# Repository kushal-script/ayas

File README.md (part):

# Ayas · अयस्

*Every surface, seen true.*

**On-device visual QC for steel and metal surfaces.**

Raspberry Pi 5 · 5-frame LED burst with a quality gate · YOLOv8n · rules informed by EN 10163-2 / ISO 7788 · Llama 3.2 1B via ExecuTorch on the Arm CPU. **Built with Llama.**

This is an entry to the Arm **Bharat AI-SoC Challenge 2026-27**, PS5 Manufacturing (real-time surface-defect detection and QC assistant).

**Phase 1** has two parts:
- a **Blender digital-twin proof of concept** of a capture method that is robust to lighting;
- the **full pipeline running on the Pi**, with twin captures as the camera.

Real-camera validation is Phase 2.

## What it does

1. **Capture.** There are two device modes:
   - the product is a **clip-on hood with a low-angle LED ring**;
   - **open handheld** with two LED pods.

   Each capture is a **5-frame raw burst** of lit and LEDs-off frames. From it the device:
   - subtracts the ambient light;
   - removes glare;
   - runs a **quality gate** that answers PASS / PASS_FLAGGED / **RETAKE**, so it asks again instead of guessing.
2. **Detect.** The plate is rectified to a 0.08 mm/px grid and cut into 640 px tiles. **YOLOv8n** finds 6 classes: scratch, dent, pit, corrosion, crack and stain. It runs on the **Hailo-10H** (AI HAT+ 2, `models/v8n_burst.hef`, 47 ms per plate), or in ONNX Runtime on the Cortex-A76 without the HAT.
3. **Judge.** A rules engine (`configs/spec_steel.yaml`) sets severity and the verdict: PASS / CLEAN_AND_REINSPECT / REWORK / HOLD_FOR_QA / REJECT.
   - The thresholds are illustrative, informed by EN 10163-2 / ISO 7788, ISO 8501 and IS 2062.
   - Confidence is not severity: a detection below 0.5 means HOLD_FOR_QA. A low-confidence crack keeps REJECT only when the inspection's second burst confirms it; otherwise it is held.
   - Open mode never certifies: PASS and CLEAN_AND_REINSPECT become HOLD_FOR_QA until the hood is fitted.
4. **Record.** Each inspection gives one JSON record (`ayas.inspection/3.0`), a row in the SQLite log and an overlay image.
5. **Advise.** **Llama 3.2 1B Instruct via ExecuTorch** on the CPU works from the JSON record. The rules engine writes the verdict, the measurements and the steps. Llama adds the likely cause and prevention, and answers the operator's follow-up questions.
   - It never changes the verdict.
   - If it is unavailable, a labelled template answers instead.

6. **Measure in 3D (on demand).** The **3D** button rebuilds the surface of each dent, pit and scratch from the burst's left and right LED frames (`app/surface3d.py`). A physics-informed height field is fitted per defect (`physics/depth_pinn.py`), in parallel worker processes. The screen shows a rotatable height map with the depth and its uncertainty. It is a measurement aid; the verdict never depends on it.
   - Twin dent plate, under the hood in dark room, window and direct sun: the 0.331 mm dent reads 0.30–0.34 mm and the 0.168 mm dent 0.15–0.16 mm; a 0.31 mm gouge reads 0.36 mm. Pits read shallow and are shown as indicative.
   - On the Pi: about 15 s for a plate with 5 relief defects, with the first surface on screen after about 8 s (it was 55 s before the speed-up).

Vision (Pipeline A) and Llama (Pipeline B) are **separate pipelines** that exchange only the JSON record.

## Results

All accuracy numbers are from the physically based **digital twin** (Blender 5.2 renders with the device's sensor-noise model). Real steel specimens are Phase 2. All timing and memory numbers are **measured on the Raspberry Pi 5**. Full tables: `reports/` and the project report.

### 1. Headline

| What | Result |
|---|---|
| Lighting robustness (hood, dark room to direct sun) | Wrong verdict with no warning in **2 of 210** captures, **0 unsafe**; the old single-frame method had 14 of 210 |
| Defect recall (hood, all 7 conditions) | scratch 1.00 · dent 1.00 · crack 0.98 · corrosion 0.83 · stain 0.80 · pit 0.79 |
| Camera to verdict on the Pi 5 | **1.7 s p50** with the detector on the Hailo-10H (**47 ms**, 28× faster than the CPU) |
| Llama 3.2 1B via ExecuTorch on the Pi | First token **5.4 s**, **11 tokens/s**, cause note in 10.3 s; 9 of 9 notes passed the guardrail |
| 3D dent depth (PINN) | **0.053 mm** error with the L/R LEDs, **0.021 mm** with a 6-sector ring |
| Device software = evaluated pipeline | **28 / 28** verdicts on the Pi |
| Product hardware | 13 boards: **ERC 0, DRC 0, 0 unconnected**; **0 interference** across 318 component models in the housing |
| Tests | **869 passed**, 12 skipped |

### 2. Lighting experiment (pre-registered)

**Set-up:**
- 15 unseen test plates (seeds ≥ 900100: never trained, tuned or calibrated on), 6 materials, 3 defect-free.
- 7 lighting conditions: C0 dark room, C1 office (~350 lux), C2 warm bulb close by, C3 window daylight, C4 low side lamp with a hand shadow, C5 a lamp reflected in the plate, C6 direct sun (~45,000 lux).
- Hood and open device, 2 variants each, 2 capture methods: **840 captures**.

**Pass criterion (fixed before the test):**
- **Hood (the product), every condition:**
  - retake ≤ 5 %;
  - F1 ≥ F1(dark) − 0.05;
  - verdict agreement with the dark room ≥ 95 %;
  - **0 silent failures** (the gate accepts and the verdict is wrong).
- **Open device:** 0 silent failures.

| Method | Device | Wrong, no warning | Unsafe¹ | Retakes | F1 |
|---|---|---|---|---|---|
| New (5-frame burst + gate) | **hood (product)** | **2 / 210** | **0** | 0 / 210 | 0.83–0.85 |
| New (5-frame burst + gate) | open | 12 / 210 | 2 | 142 / 210 | 0.72–0.89 |
| Old (one auto-exposed frame) | hood | 14 / 210 | 0 | no gate | 0.91–0.92 |
| Old (one auto-exposed frame) | open | 16 / 210 | 0 | no gate | 0.80–0.91 |

¹ Milder than the truth and not held.

**New method, per condition** (P / R / F1 over accepted captures; verdict agreement with the dark room and with the truth; |Δ| = mean image difference from the dark room in sensor counts):

| Condition | Lux | Retakes (main reason) | Precision | Recall | F1 | Verdict = dark | Verdict = truth | Silent (unsafe) | \|Δ\| (DN) |
|---|---|---|---|---|---|---|---|---|---|
| C0 dark room, **hood** | 0 | 0/30 | 0.78 | 0.89 | 0.83 | 30/30 | 30/30 | 0 (0) | 0.0 |
| C1 office, **hood** | 353 | 0/30 | 0.78 | 0.91 | 0.84 | 29/30 | 29/30 | 1 (0) | 2.8 |
| C2 warm bulb, **hood** | 648 | 0/30 | 0.78 | 0.91 | 0.84 | 30/30 | 30/30 | 0 (0) | 2.7 |
| C3 window daylight, **hood** | 3,569 | 0/30 | 0.79 | 0.91 | 0.85 | 30/30 | 30/30 | 0 (0) | 2.7 |
| C4 side lamp + hand shadow, **hood** | 2,005 | 0/30 | 0.79 | 0.91 | 0.85 | 29/30 | 29/30 | 1 (0) | 2.8 |
| C5 lamp reflected in the plate, **hood** | 514 | 0/30 | 0.78 | 0.91 | 0.84 | 30/30 | 30/30 | 0 (0) | 2.8 |
| C6 direct sun, **hood** | 44,872 | 0/30 | 0.77 | 0.89 | 0.83 | 30/30 | 30/30 | 0 (0) | 2.7 |
| C0 dark room, open | 0 | 6/30 (saturated) | 0.81 | 0.82 | 0.82 | 24/24 | 20/24 | 4 (0) | 0.0 |
| C1 office, open | 353 | 17/30 (changed) | 0.80 | 0.72 | 0.76 | 11/13 | 9/13 | 4 (2) | 2.8 |
| C2 warm bulb, open | 648 | 13/30 (changed) | 0.77 | 0.85 | 0.81 | 16/17 | 16/17 | 1 (0) | 2.7 |
| C3 window daylight, open | 3,569 | 26/30 (glare + ambient) | 0.92 | 0.86 | 0.89 | 4/4 | 4/4 | 0 (0) | 3.4 |
| C4 side lamp + hand shadow, open | 2,005 | 27/30 (changed) | 0.89 | 0.73 | 0.80 | 3/3 | 3/3 | 0 (0) | 3.0 |
| C5 lamp reflected, open | 514 | 23/30 (glare + ambient) | 0.76 | 0.68 | 0.72 | 7/7 | 4/7 | 3 (0) | 3.1 |
| C6 direct sun, open | 44,872 | 30/30 (too bright) | – | – | – | – | – | 0 (0) | – |

**With the hood:**
- Every condition from dark to direct sun meets the retake, F1 and agreement limits.
- False alarms on defect-free plates: **0** (the old method: 0.33 per plate).
- The processed image differs from the dark room by 2.7–2.8 DN in every condition, about the sensor-noise level, even in direct sun.
- **Caveat:** in the twin a seated hood is light-tight by construction, so these rows test repeatability, not light leakage. Real-world leakage is the first Phase 2 measurement.

**Strict result: FAIL by 2 captures.**
- Both are one low-confidence (0.27 / 0.32) false "crack" on unlabelled mill-scale texture at a plate edge. It gave REJECT where the truth is HOLD_FOR_QA: stricter than the truth, not unsafe.
- The score does not follow the light level (Spearman ρ = 0.15), so the cause is the model, not the lighting.

**Fixes adopted (22 Nov):**
- **Two-burst confirmation (P1h).** Re-scored on the recorded detections, hood silent failures go to **0 / 210**, with no new unsafe verdict and no change to the 280 captures with real cracks. It still needs confirming on fresh plates.
- **Hood-only certification.** Without the hood, the gate refuses 142 of 210 bright scenes (every direct-sun capture), and dark mill scale caused 2 unsafe misses. Open mode now never certifies.

### 3. Detection quality (new method, hood, all 7 conditions pooled)

| Class | Recall |
|---|---|
| scratch | 126 / 126 = **1.00** |
| dent | 70 / 70 = **1.00** |
| crack | 82 / 84 = **0.98** |
| corrosion | 70 / 84 = 0.83 |
| stain | 56 / 70 = 0.80 |
| pit | 77 / 98 = 0.79 |

- **Precision** is 0.77–0.79 (the old method: 0.90). Part of the gap is detections of real defects that the ground truth marks "not visible" and counts as false positives.
- **Detector:** YOLOv8n trained from COCO for 150 epochs on 5,176 / 430 tiles from 800 twin scenes. ONNX and PyTorch agree to 0.0013 on the raw output.

### 4. On the Raspberry Pi 5

| Metric | Pi 5 + Hailo-10H | Pi 5, CPU only (ONNX Runtime) | Mac M3 CPU (reference) |
|---|---|---|---|
| Camera to verdict, p50 / p95 | **1,665 / 2,106 ms** | 2,856 / 3,331 ms | 617 / 716 ms |
| Detector per inspection | **47 ms** | 1,329 ms | – |
| Throughput | 0.57 inspections/s | 0.39 inspections/s | 1.8 inspections/s |
| Peak memory (app) | 0.98 GB | 1.08 GB | 1.7 GB |
| Verdicts equal to the twin evaluation | 27 / 28¹ | **28 / 28** | 28 / 28 |
| CPU temperature | 51–67 °C, no throttling | | |

¹ The one difference is the edge false positive of §2, which the INT8 model happens not to fire: a side effect of quantisation, not a fix.

**Vision stages on the CPU, p50 ms** (from the Llama benchmark run, `reports/pi_llm_final4_20261122-183748/`; the Hailo run is in `reports/pi_phase1_raspberrypi_20261122-201042/`):

| Stage | capture | process | rectify | tile | detect | merge | measure | rules | report | image | total |
|---|---|---|---|---|---|---|---|---|---|---|---|
| ms | 561 | 1,135 | 5.4 | 4.1 | 1,337 | 0.3 | 8.8 | 0.2 | 0.3 | 7.5 | 2,866 |

### 5. Llama 3.2 1B Instruct via ExecuTorch (on the Pi's Cortex-A76)

**Speed** (`reports/pi_llm_final4_20261122-183748/`, 16 inspections):

| Metric | p50 | p95 |
|---|---|---|
| Time to first token (model clock) | 5,429 ms | 5,505 ms |
| First text on screen (wall, incl. 2.5 s load) | 8,029 ms | 8,100 ms |
| Decode speed | 11.0 tokens/s | 11.4 tokens/s |
| Prefill speed | 112.5 tokens/s | 113.3 tokens/s |
| Whole cause note | 10.3 s | 11.1 s |
| Camera to advice | 13.5 s | 13.9 s |
| Prompt / generated tokens | 611 / 29 | 611 / 41 |
| Peak memory of the runner | 1.38 GB | |

**First design against final design:**

| | First design | Final design |
|---|---|---|
| Who writes the facts | Llama restates the whole record | The rules engine; Llama writes cause and prevention |
| Prompt | ~1,340 tokens (JSON) | 611 tokens |
| First token | 15.8 s | 5.4 s |
| Decode | 6.7 tokens/s | 11.0 tokens/s |
| Time per answer | ~54 s | 10.3 s |
| Answers with a factual error | 3 of 7 | 0 of 9 |

- Every verdict on screen was right in both designs, because the verdict comes from the rules engine.
- In the final run, the 7 RETAKE and PASS results were answered by the rules engine.
- "How to fix?" and override requests ("Can I paint over the crack and ship it?") always get the rules engine's exact answer.
- Open questions take 31–35 s and are general: the weakest part, Phase 2 work.

### 6. 3D depth: physics-informed neural network (PINN)

**Forward model against Blender** (no fitted parameters):
- **Open pods:** flat metal within 0.1–0.9 % at the median; ball dents within 0.2–1.1 %, pixel correlation ≥ 0.99.
- **Hood:** the direct model under-predicts flat metal by 2–57 %. A black-hood control closes most of the gap (aluminium 0.85 / 0.76 → 0.96 / 0.94), which shows the cause is the hood's own inter-reflection. A one-bounce hood model reproduces it at dents (correlation 0.88–0.94).

**Depth on 96 twin dents and pits** (6 materials, sensor noise):

| | L/R halves (today) | 3 sectors | 6 sectors |
|---|---|---|---|
| PINN, dents, MAE | **0.053 mm** | 0.034 mm | **0.021 mm** |
| PINN, dents within 0.05 mm | 62 % | 79 % | 92 % |
| Classical slopes + Poisson, dents, MAE | 0.153 mm | 0.089 mm | 0.071 mm |
| PINN, pits, MAE (bias) | 0.154 mm (−0.154) | 0.114 mm | 0.107 mm |

- **Against the classical method:** the PINN is 2.1–3.4× better on dents and 1.5–1.8× on pits. Pits are under-estimated (28–88 %) and shown as indicative only.
- **Lighting-invariant with the hood:** across all 7 conditions, dent depth changes by at most 0.023 mm.
- **Twin dent plate, dark room to direct sun:** the 0.331 mm dent reads 0.30–0.34 mm, the 0.168 mm dent 0.15–0.16 mm, and a 0.31 mm gouge 0.36 mm.
- **Severity safety:** under the proposed rule (use a depth only if the fit converged and the 90 % interval is ≤ 0.08 mm), no depth-based decision was more lenient than the decision with the true depth: 0 of 89 coupon decisions and 0 of 7 pilot decisions.
- **On the Pi:** about 15 s for a plate with 5 relief defects, first surface after about 8 s (it was 55 s before the speed-up).

### 7. Experiments tried and not adopted

**I-JEPA anomaly head** (region AUROC, burst capture):

| Method | Hood | Open |
|---|---|---|
| jepa_pred (predictor error) | **0.975** | 0.957 |
| ResNet18 PatchCore | 0.965 | 0.957 |
| ViT-Tiny (ImageNet) kNN | 0.919 | 0.923 |
| Pixels kNN | 0.919 | 0.858 |
| jepa_knn (EMA target + memory bank) | 0.508 | 0.563 |

- Not adopted. It did not beat ResNet18 by the pre-set +0.02 (+0.010 hood, +0.000 open).
- It was less lighting-invariant (open retrieval@1: 0.853 against 0.967).
- It is too slow for the Pi (350–580 ms per crop against a 150 ms budget).

**Depth network:** a U-Net fine-tuned on Blender crops. Dent error 0.149 mm (pit 0.096, scratch 0.041) against 0.022 mm for the PINN: not adopted (`models/depthnet_blender.onnx`).

### 8. Optimisations (measured)

| Technique | Before → after |
|---|---|
| Detector: INT8 + Hailo-10H HEF with on-chip NMS | 1,329 → **47 ms** per inspection (28×); camera to verdict 2.86 → 1.67 s |
| Llama: SpinQuant INT4 + ExecuTorch XNNPACK | 1B model in a 1.08 GB `.pte`, 1.38 GB RAM, 11 tokens/s on the CPU |
| Llama: facts to the rules engine, a short plain-text prompt | Prompt 1,340 → 611 tokens; first token 15.8 → 5.4 s; answer ~54 → 10.3 s; errors 3/7 → 0/9 |
| 3D: fast mode, warm worker pool, one defect per core | Plate with 5 defects 55 → 15 s |
| Capture-side invariance instead of a bigger network | A ~3 M-parameter detector holds across 7 lighting conditions |

### 9. Product hardware (Phase 2)

| Check | Result |
|---|---|
| Schematics (ERC), 13 boards | 0 errors, 0 warnings |
| Layouts (DRC), 13 boards | 0 violations, 0 unconnected pads (LIGHT/IO 6-layer, 0.1 mm rules) |
| Design consistency (`tests/test_hardware_design.py`) | 43 passed: matched cable pinouts, palindrome flex, no swappable connectors, no dangling nets |
| Mechanical fit (Fusion 360) | 318 board component models, 0 interference with the housing, buttons, Pi, display, fan or bank; no floating parts |
| Housing | 268 mm wide, about 900 g of PETG; every service screw into a heat-set insert |

## Architecture and demo

- **Architecture** of the system, every model, the data contract and the electronics: [docs/ARCHITECTURE.md](docs/ARCHITECTURE.md).
- **2-minute product demo video:** [reports/Ayas_demo_1080p.mp4](reports/Ayas_demo_1080p.mp4) (sources in `tools/video/`).
- **Models:** `models/` holds the detector ONNX and Hailo HEF and the depth-network ONNX; `models/README.md` says how the Llama `.pte` was made.

## Project report

**[docs/report/Ayas_Project_Report.pdf](docs/report/Ayas_Project_Report.pdf)** (also `.docx`) covers the methodology, the AI models, the results, hardware utilisation, optimisation techniques, the 3D model and the PCBs. It is generated by `tools/report/` from the numbers in `reports/` and `docs/`.

Authors: Binay Verma, Dhanush D, Kushal S. Faculty mentor: Dr. Subir Roy.

## Phase 2 product hardware

- **Housing:** a parametric Fusion 360 model (`hardware/enclosure/ayas_handheld_fusion.py`): a two-grip handheld, 268 mm wide, with two toed-in LED pods, the camera on the centre line, a 5-inch touch display on the back and a clip-on light-tight inspection hood. Every service screw goes into a heat-set insert.
- **Full assembly:** `hardware/enclosure/ayas_assembly_fusion.py` places every KiCad board as its 3D model and draws the cable harness. All 318 board component models fit with no interference. Renders: `docs/hardware/renders/`.
- **13 PCBs** generated from one description, `hardware/pcb/design.py` (KiCad 10, auto-routed with Freerouting). Every board passes ERC and DRC with nothing unrouted:
  - **POWER** (2-layer): USB-C PD sink to 12 V, a 5 V / 5 A buck for the Pi, LED-rail monitor, power-hold with no standby drain, and charge-through.
  - **LIGHT/IO** (6-layer): an RP2040 with 10 constant-current LED sinks, the UV interlock, buttons, fan and buzzer.
  - **Pods:** UV pod hubs (9 plug-in UV LEDs each) and WHITE-L / WHITE-R carriers for three 12 V white LED modules each.
  - **Docking:** the pod flex with its docks, and the hood dock and pad on spring pins.
  - **SIDE-L / SIDE-R** button boards and the **CHARGE** port board.
- **Controls, power and export:** `docs/hardware/controls.md`. **Board specification:** `docs/hardware/pcb_phase2.md`. **Service manual** (fasteners, cable table, assembly order, repairs): `docs/hardware/service.md`.
- **Checked by** `tests/test_hardware_design.py`: both ends of every cable carry the same pinout, flex pinouts are palindromes, and no two different connectors on one board take the same plug.

## Gallery

Every image of the project: the product, how it works, the architecture, the results, and every PCB with its schematic. Click an image for full size.

### The product

<table><tr><td><br><sub>Back: display, thumb buttons, USB-A export</sub></td><td><br><sub>With the inspection hood fitted</sub></td></tr>
<tr><td><br><sub>X-ray, front: boards, LED modules and harness</sub></td><td><br><sub>X-ray, back: POWER, LIGHT/IO, Pi stack, bank, fan</sub></td></tr>
<tr><td><br><sub>X-ray, top: harness routes</sub></td><td><br><sub>Cutaway from the back, shell at 25 %</sub></td></tr>
<tr><td><br><sub>Product render (demo video)</sub></td><td><br><sub>Exploded view (demo video)</sub></td></tr></table>

### How it works

<table>
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
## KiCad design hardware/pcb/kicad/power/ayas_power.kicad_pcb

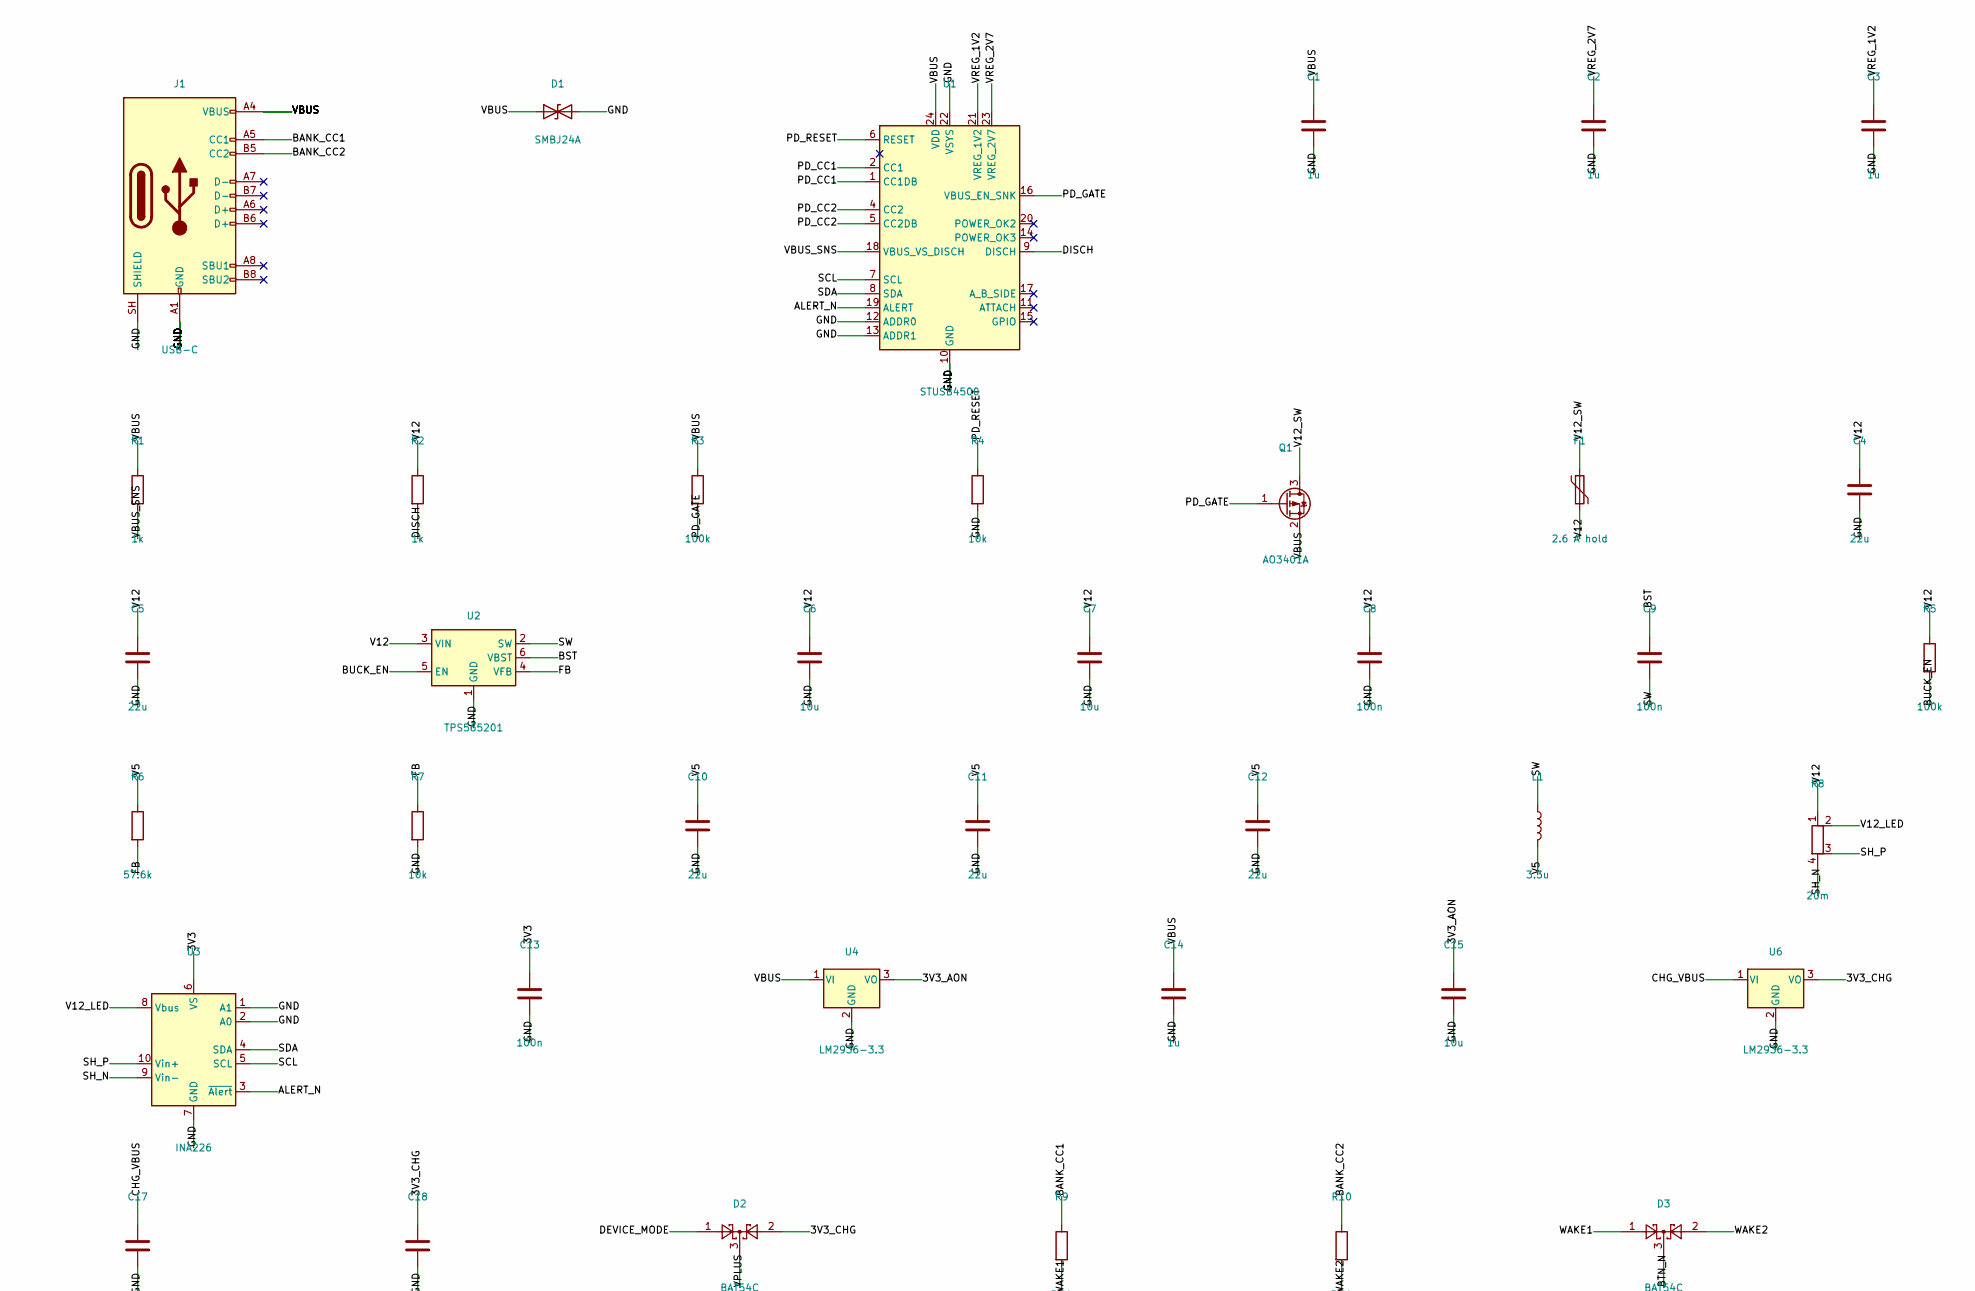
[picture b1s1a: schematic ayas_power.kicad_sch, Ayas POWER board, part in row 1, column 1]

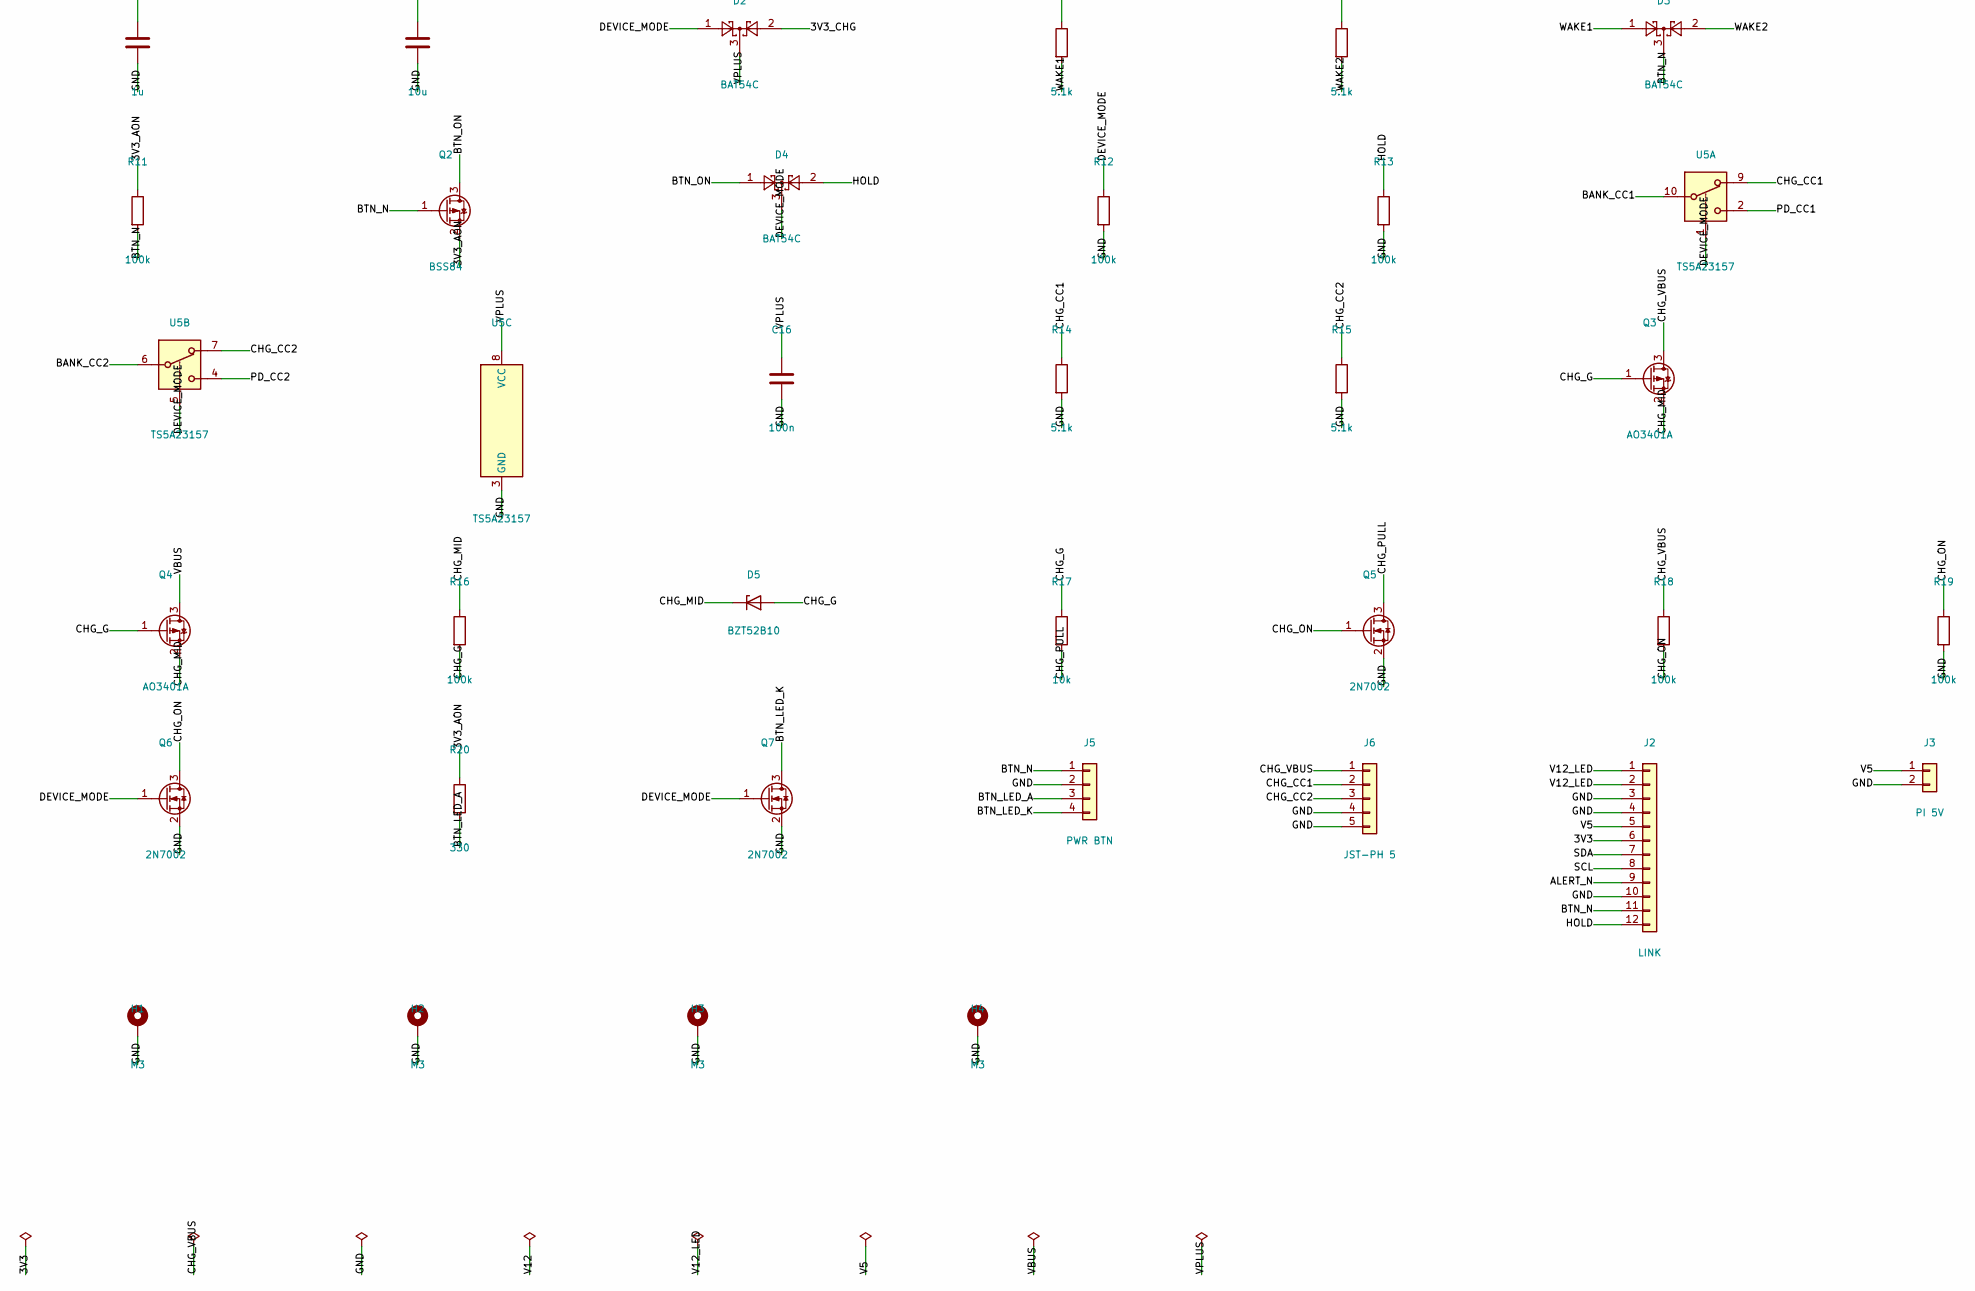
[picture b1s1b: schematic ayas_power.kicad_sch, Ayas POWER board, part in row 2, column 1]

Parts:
C1, C2, C3: 1u; C_0603_1608Metric
C4, C5: 22u; C_1210_3225Metric; MPN 25 V X5R
C6, C7: 10u; C_1206_3216Metric; MPN 25 V
C8, C9, C13, C16: 100n; C_0603_1608Metric
C10, C11, C12: 22u; C_1206_3216Metric; MPN 10 V X5R
C14, C17: 1u; C_0805_2012Metric; MPN 50 V
C15: 10u; C_0805_2012Metric; MPN LM2936 needs >= 10 uF out
C18: 10u; C_0805_2012Metric
D1: SMBJ24A; D_SMB; MPN SMBJ24A (Littelfuse)
D2, D3, D4: BAT54C; SOT-23; MPN BAT54C (Nexperia)
D5: BZT52B10; D_SOD-123F; MPN BZT52B10 (Nexperia)
F1: 2.6 A hold; Fuse_1812_4532Metric; MPN MF-MSMF260-2 (Bourns)
H1, H2, H3, H4: M3; MountingHole_3.2mm_M3_DIN965_Pad
J1: USB-C; USB_C_Receptacle_GCT_USB4105-xx-A_16P_TopMnt_Horizontal; MPN GCT USB4105-GF-A
J2: LINK; JST_PH_B12B-PH-K_1x12_P2.00mm_Vertical; MPN B12B-PH-K-S (JST)
J3: PI 5V; JST_VH_B2P-VH_1x02_P3.96mm_Vertical; MPN B2P-VH (JST)
J5: PWR BTN; JST_PH_B4B-PH-K_1x04_P2.00mm_Vertical; MPN B4B-PH-K-S (JST)
J6: JST-PH 5; JST_PH_B5B-PH-K_1x05_P2.00mm_Vertical; MPN B5B-PH-K-S (JST)
L1: 3.3u; L_Bourns_SRP7028A_7.3x6.6mm; MPN SRP7028A-3R3M (Bourns, 9 A sat)
Q1, Q3, Q4: AO3401A; SOT-23; MPN AO3401A (AOS)
Q2: BSS84; SOT-23; MPN BSS84 (Nexperia)
Q5, Q6, Q7: 2N7002; SOT-23; MPN 2N7002 (Nexperia)
R1: 1k; R_0603_1608Metric
R2: 1k; R_1206_3216Metric
R3, R5, R11, R12, R13, R16, R18, R19: 100k; R_0603_1608Metric
R4, R7, R17: 10k; R_0603_1608Metric
R6: 57.6k; R_0603_1608Metric
R8: 20m; R_Shunt_Vishay_WSK2512_6332Metric_T1.19mm; MPN WSK2512R0200FEA (Vishay)
R9, R10, R14, R15: 5.1k; R_0603_1608Metric
R20: 330; R_0603_1608Metric
U1: STUSB4500; QFN-24-1EP_4x4mm_P0.5mm_EP2.6x2.6mm; MPN STUSB4500QTR (ST)
U2: TPS565201; SOT-23-6; MPN TPS565201DDCR (TI)
U3: INA226; MSOP-10_3x3mm_P0.5mm; MPN INA226AIDGSR (TI)
U4, U6: LM2936-3.3; SOT-223-3_TabPin2; MPN LM2936MP-3.3 (TI)
U5: TS5A23157; TSSOP-10_3x3mm_P0.5mm; MPN TS5A23157DGSR (TI)

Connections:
3V3: C13.1, J2.6, U3.6 (VS)
3V3_AON: C15.1, Q2.2 (S), R11.1, R20.1, U4.3 (VO)
3V3_CHG: C18.1, D2.2, U6.3 (VO)
ALERT_N: J2.9, U1.19 (ALERT), U3.3 (~Alert)
BANK_CC1: J1.A5 (CC1), R9.1, U5.10
BANK_CC2: J1.B5 (CC2), R10.1, U5.6
BST: C9.1, U2.6 (VBST)
BTN_LED_A: J5.3, R20.2
BTN_LED_K: J5.4, Q7.3 (D)
BTN_N: D3.3, J2.11, J5.1, Q2.1 (G), R11.2
BTN_ON: D4.1, Q2.3 (D)
BUCK_EN: R5.2, U2.5 (EN)
CHG_CC1: J6.2, R14.1, U5.9
CHG_CC2: J6.3, R15.1, U5.7
CHG_G: D5.2 (A), Q3.1 (G), Q4.1 (G), R16.2, R17.1
CHG_MID: D5.1 (K), Q3.2 (S), Q4.2 (S), R16.1
CHG_ON: Q5.1 (G), Q6.3 (D), R18.2, R19.1
CHG_PULL: Q5.3 (D), R17.2
CHG_VBUS: C17.1, J6.1, Q3.3 (D), R18.1, U6.1 (VI)
DEVICE_MODE: D2.1, D4.3, Q6.1 (G), Q7.1 (G), R12.1, U5.1, U5.5
DISCH: R2.2, U1.9 (DISCH)
FB: R6.2, R7.1, U2.4 (VFB)
GND: C1.2, C2.2, C3.2, C4.2, C5.2, C6.2, C7.2, C8.2, C10.2, C11.2, C12.2, C13.2, C14.2, C15.2, C16.2, C17.2, C18.2, D1.2 (A2), H1.1, H2.1, H3.1, H4.1, J1.A1 (GND), J1.A12 (GND), J1.B1 (GND), J1.B12 (GND), J1.SH (SHIELD), J2.3, J2.4, J2.10, J3.2, J5.2, J6.4, J6.5, Q5.2 (S), Q6.2 (S), Q7.2 (S), R4.2, R7.2, R12.2, R13.2, R14.2, R15.2, R19.2, U1.10 (GND), U1.12 (ADDR0), U1.13 (ADDR1), U1.22 (VSYS), U1.25 (GND), U2.1 (GND), U3.1 (A1), U3.2 (A0), U3.7 (GND), U4.2 (GND), U5.3 (GND), U6.2 (GND)
HOLD: D4.2, J2.12, R13.1
PD_CC1: U1.1 (CC1DB), U1.2 (CC1), U5.2
PD_CC2: U1.4 (CC2), U1.5 (CC2DB), U5.4
PD_GATE: Q1.1 (G), R3.2, U1.16 (VBUS_EN_SNK)
PD_RESET: R4.1, U1.6 (RESET)
SCL: J2.8, U1.7 (SCL), U3.5 (SCL)
SDA: J2.7, U1.8 (SDA), U3.4 (SDA)
SH_N: R8.4, U3.9 (Vin-)
SH_P: R8.3, U3.10 (Vin+)
SW: C9.2, L1.1, U2.2 (SW)
V5: C10.1, C11.1, C12.1, J2.5, J3.1, L1.2, R6.1
V12: C4.1, C5.1, C6.1, C7.1, C8.1, F1.2, R2.1, R5.1, R8.1, U2.3 (VIN)
V12_LED: J2.1, J2.2, R8.2, U3.8 (Vbus)
V12_SW: F1.1, Q1.3 (D)
VBUS: C1.1, C14.1, D1.1 (A1), J1.A4 (VBUS), J1.A9 (VBUS), J1.B4 (VBUS), J1.B9 (VBUS), Q1.2 (S), Q4.3 (D), R1.1, R3.1, U1.24 (VDD), U4.1 (VI)
VBUS_SNS: R1.2, U1.18 (VBUS_VS_DISCH)
VPLUS: C16.1, D2.3, U5.8 (VCC)
VREG_1V2: C3.1, U1.21 (VREG_1V2)
VREG_2V7: C2.1, U1.23 (VREG_2V7)
WAKE1: D3.1, R9.2
WAKE2: D3.2, R10.2

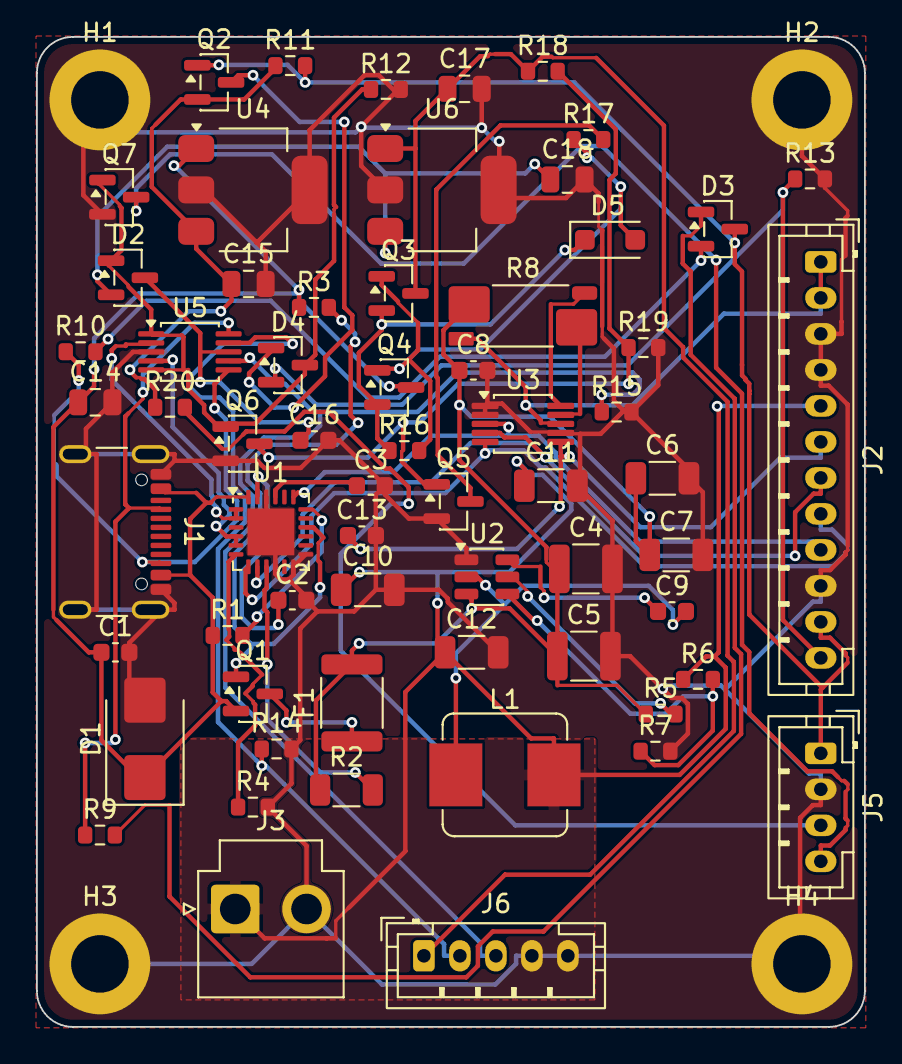
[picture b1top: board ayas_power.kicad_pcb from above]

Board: 2 copper layers, 46.0 x 55.0 mm, 67 parts (0 on the bottom side), 44 nets.

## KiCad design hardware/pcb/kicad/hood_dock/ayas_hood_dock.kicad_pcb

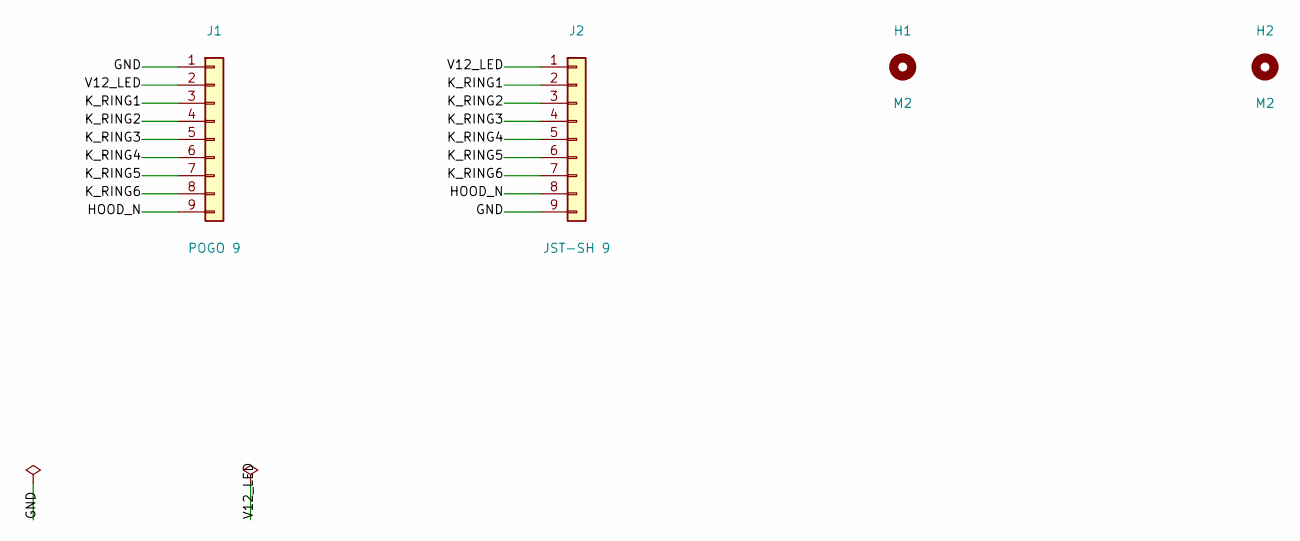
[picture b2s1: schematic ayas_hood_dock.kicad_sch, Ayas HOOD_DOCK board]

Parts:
H1, H2: M2; MountingHole_2.2mm_M2
J1: POGO 9; Pogo_1x09_P2.54mm; MPN Mill-Max 0906 series spring pins (verif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
J2: JST-SH 9; JST_SH_SM09B-SRSS-TB_1x09-1MP_P1.00mm_Horizontal; MPN SM09B-SRSS-TB (JST)

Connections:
GND: J1.1, J2.9
HOOD_N: J1.9, J2.8
K_RING1: J1.3, J2.2
K_RING2: J1.4, J2.3
K_RING3: J1.5, J2.4
K_RING4: J1.6, J2.5
K_RING5: J1.7, J2.6
K_RING6: J1.8, J2.7
V12_LED: J1.2, J2.1

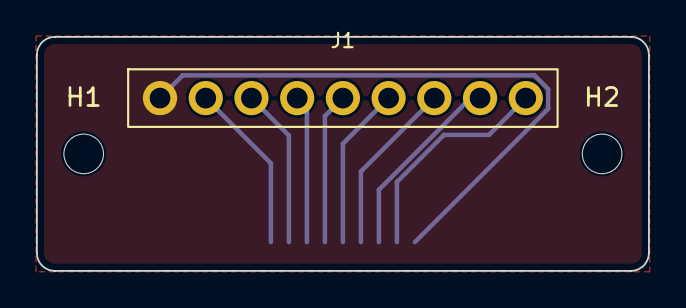
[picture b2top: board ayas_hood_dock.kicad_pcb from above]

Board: 2 copper layers, 34.0 x 13.0 mm, 4 parts (1 on the bottom side), 9 nets.

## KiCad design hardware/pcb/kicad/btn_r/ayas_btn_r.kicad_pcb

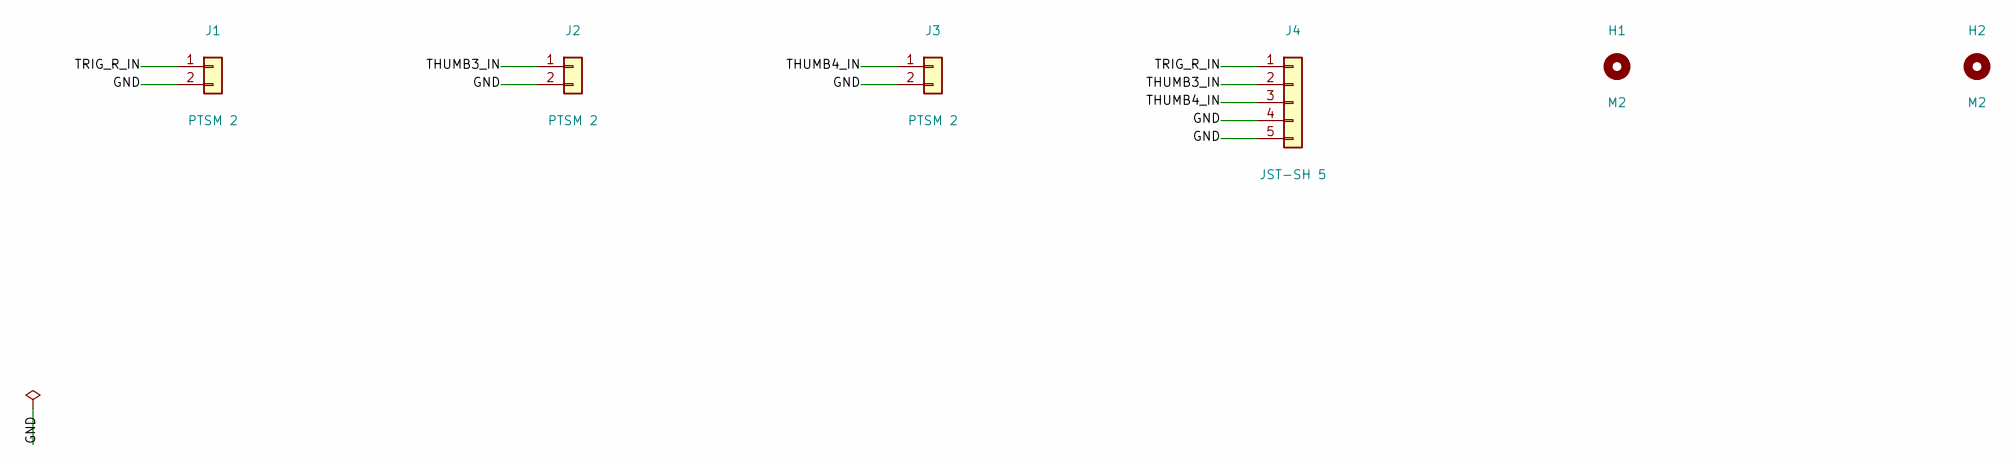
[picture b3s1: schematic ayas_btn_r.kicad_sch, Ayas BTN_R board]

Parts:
H1, H2: M2; MountingHole_2.2mm_M2
J1, J2, J3: PTSM 2; TerminalBlock_Phoenix_PTSM-0,5-2-2.5-H-THR_1x02_P2.50mm_Hor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; MPN PTSM 0,5/ 2-2,5-H THR (Phoenix Contact)
J4: JST-SH 5; JST_SH_SM05B-SRSS-TB_1x05-1MP_P1.00mm_Horizontal; MPN SM05B-SRSS-TB (JST)

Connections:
GND: J1.2, J2.2, J3.2, J4.4, J4.5
THUMB3_IN: J2.1, J4.2
THUMB4_IN: J3.1, J4.3
TRIG_R_IN: J1.1, J4.1

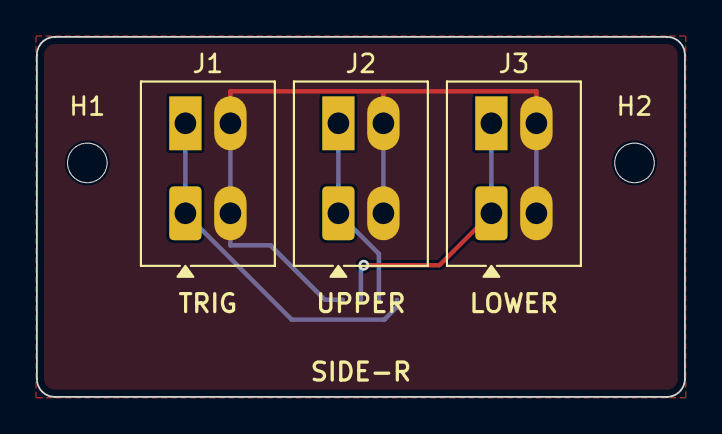
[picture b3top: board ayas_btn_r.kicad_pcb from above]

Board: 2 copper layers, 36.0 x 20.0 mm, 6 parts (1 on the bottom side), 4 nets.

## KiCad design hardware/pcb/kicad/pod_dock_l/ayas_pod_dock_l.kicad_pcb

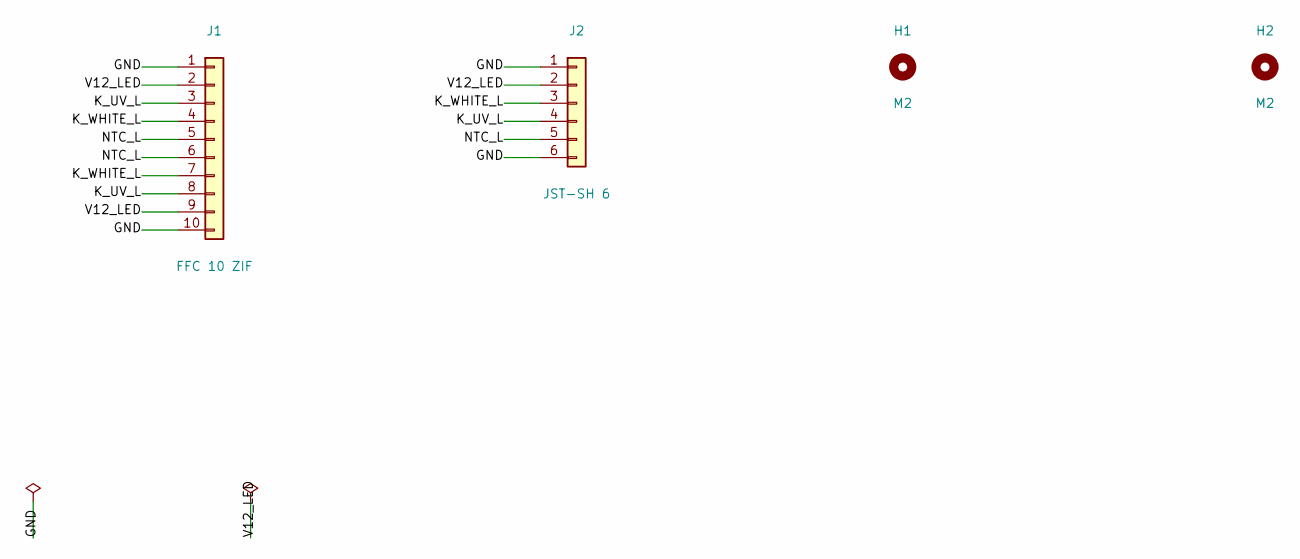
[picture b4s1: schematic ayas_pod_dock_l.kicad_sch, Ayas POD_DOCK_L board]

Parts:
H1, H2: M2; MountingHole_2.2mm_M2
J1: FFC 10 ZIF; Molex_200528-0100_1x10-1MP_P1.00mm_Horizontal; MPN 200528-0100 (Molex)
J2: JST-SH 6; JST_SH_SM06B-SRSS-TB_1x06-1MP_P1.00mm_Horizontal; MPN SM06B-SRSS-TB (JST)

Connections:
GND: J1.1, J1.10, J2.1, J2.6
K_UV_L: J1.3, J1.8, J2.4
K_WHITE_L: J1.4, J1.7, J2.3
NTC_L: J1.5, J1.6, J2.5
V12_LED: J1.2, J1.9, J2.2

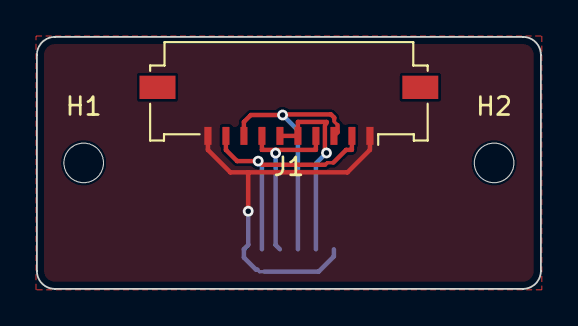
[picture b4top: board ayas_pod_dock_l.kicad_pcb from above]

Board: 2 copper layers, 28.0 x 14.0 mm, 4 parts (1 on the bottom side), 5 nets.

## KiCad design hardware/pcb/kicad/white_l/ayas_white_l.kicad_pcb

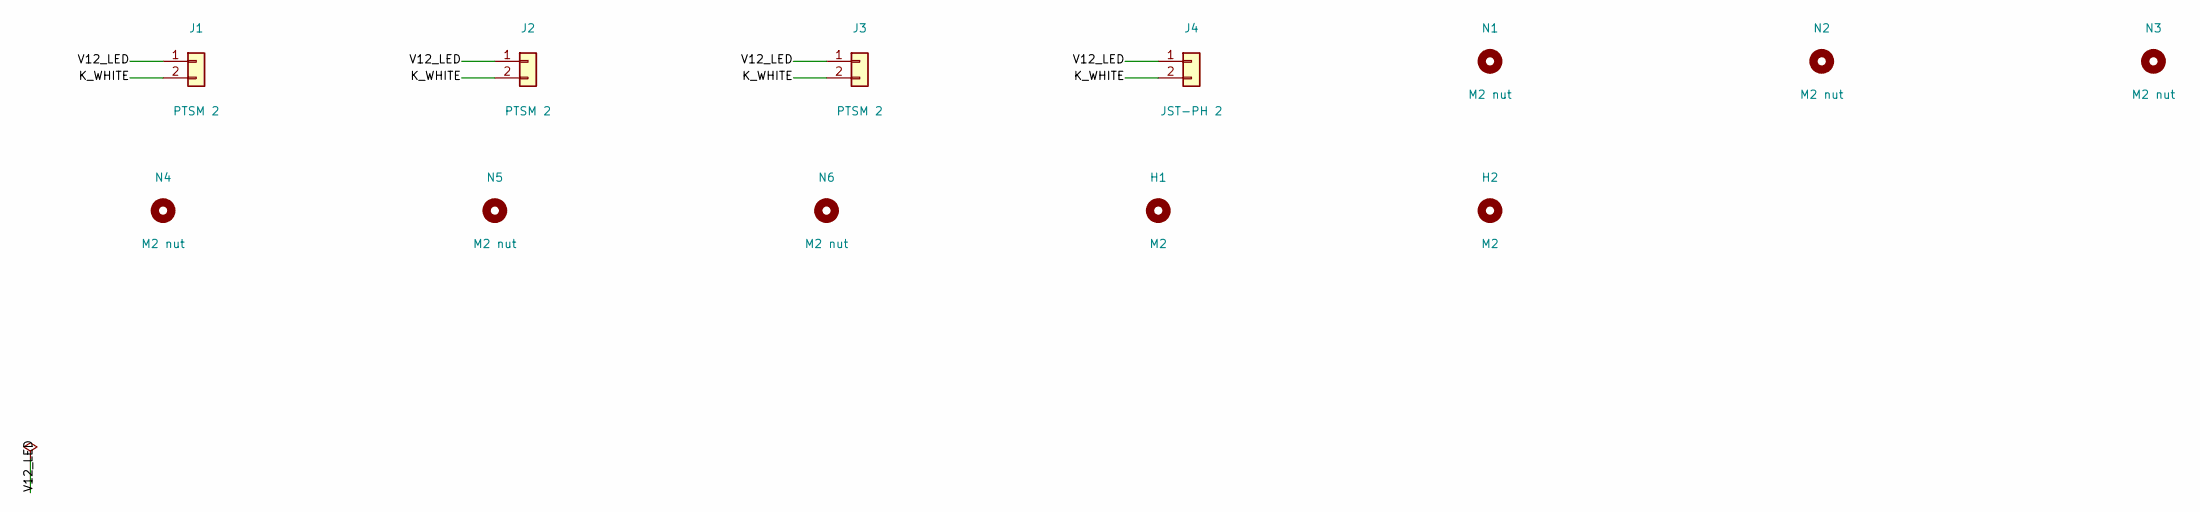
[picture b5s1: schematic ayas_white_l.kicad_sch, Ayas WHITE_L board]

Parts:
H1, H2: M2; MountingHole_2.2mm_M2
J1, J2, J3: PTSM 2; TerminalBlock_Phoenix_PTSM-0,5-2-2.5-H-THR_1x02_P2.50mm_Hor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; MPN PTSM 0,5/ 2-2,5-H THR (Phoenix Contact)
J4: JST-PH 2; JST_PH_S2B-PH-K_1x02_P2.00mm_Horizontal; MPN S2B-PH-K-S (JST)
N1, N2, N3, N4, N5, N6: M2 nut; Mounting_Wuerth_WA-SMSI-M2_H2mm_9774020243; MPN 9774020243 (Wurth WA-SMSI, M2, 2 mm)

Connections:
K_WHITE: J1.2, J2.2, J3.2, J4.2
V12_LED: J1.1, J2.1, J3.1, J4.1

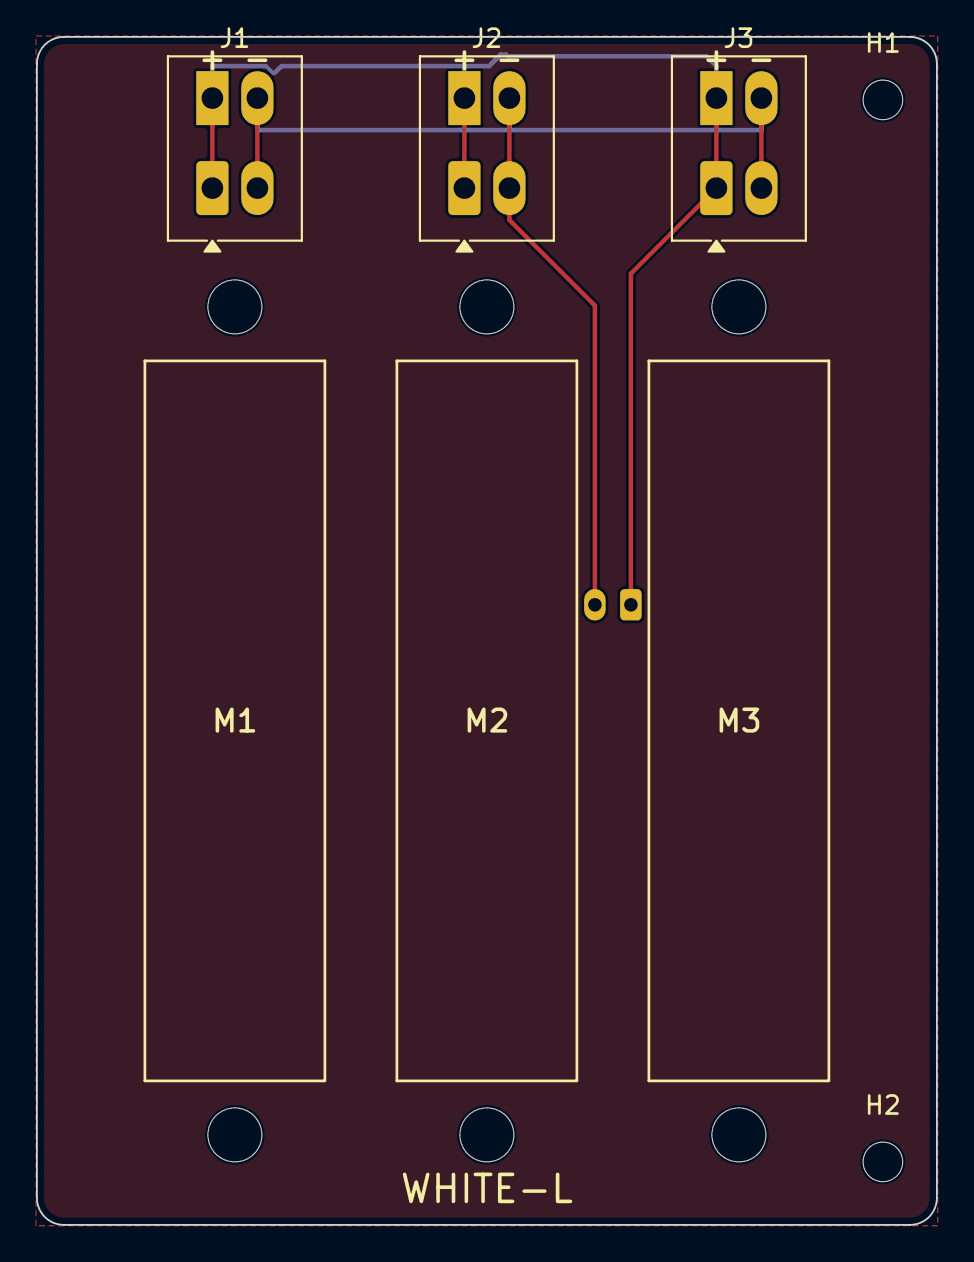
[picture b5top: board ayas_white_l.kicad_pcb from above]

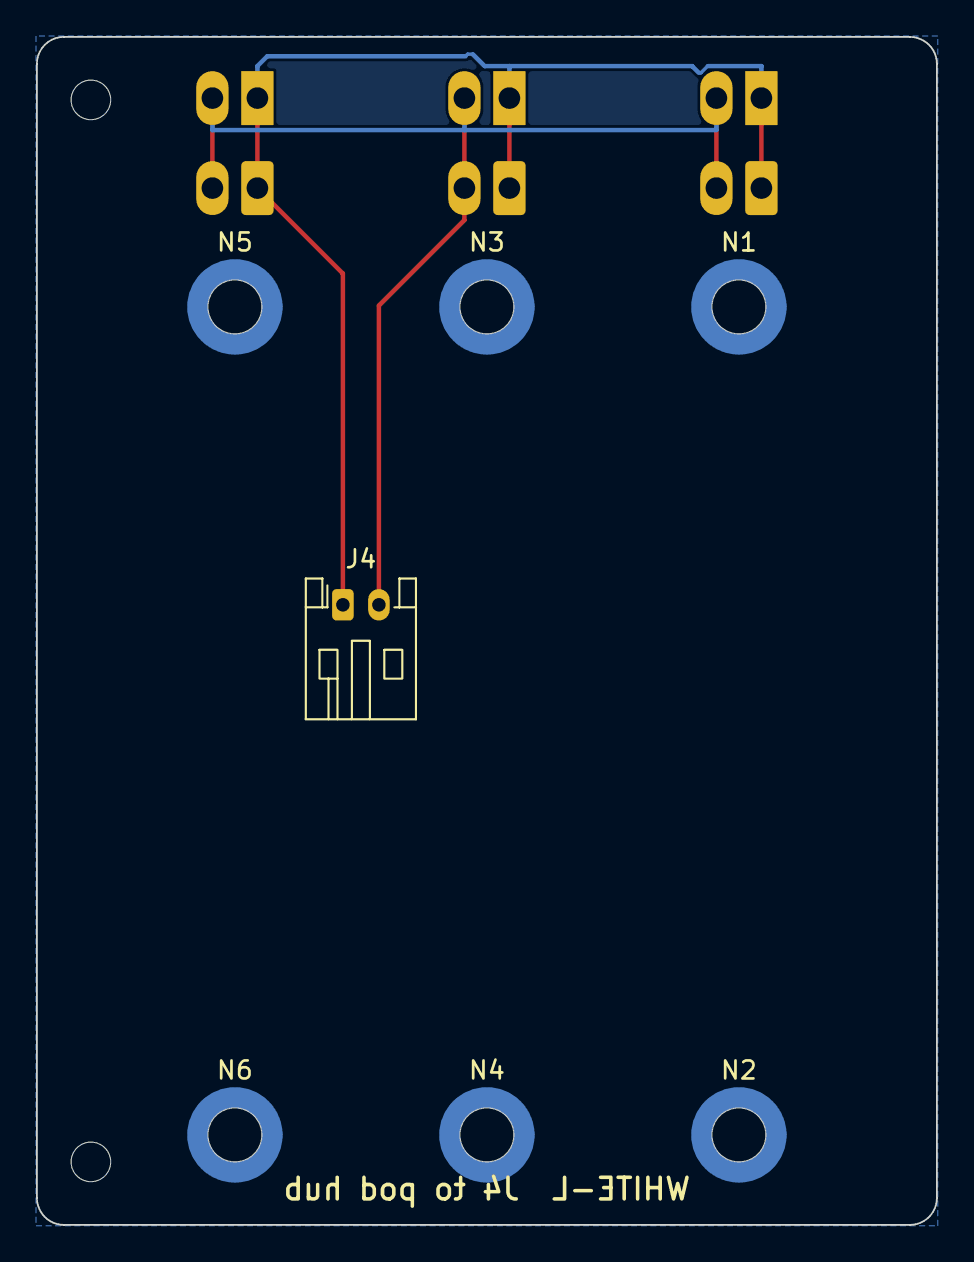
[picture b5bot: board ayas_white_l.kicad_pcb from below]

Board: 2 copper layers, 50.0 x 66.0 mm, 12 parts (7 on the bottom side), 2 nets.

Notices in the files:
README.md:
Licence:
- AGPL-3.0 (`LICENSE`).
- `NOTICE` lists the third-party software and the Llama 3.2 Community License.
- Built with Llama.
